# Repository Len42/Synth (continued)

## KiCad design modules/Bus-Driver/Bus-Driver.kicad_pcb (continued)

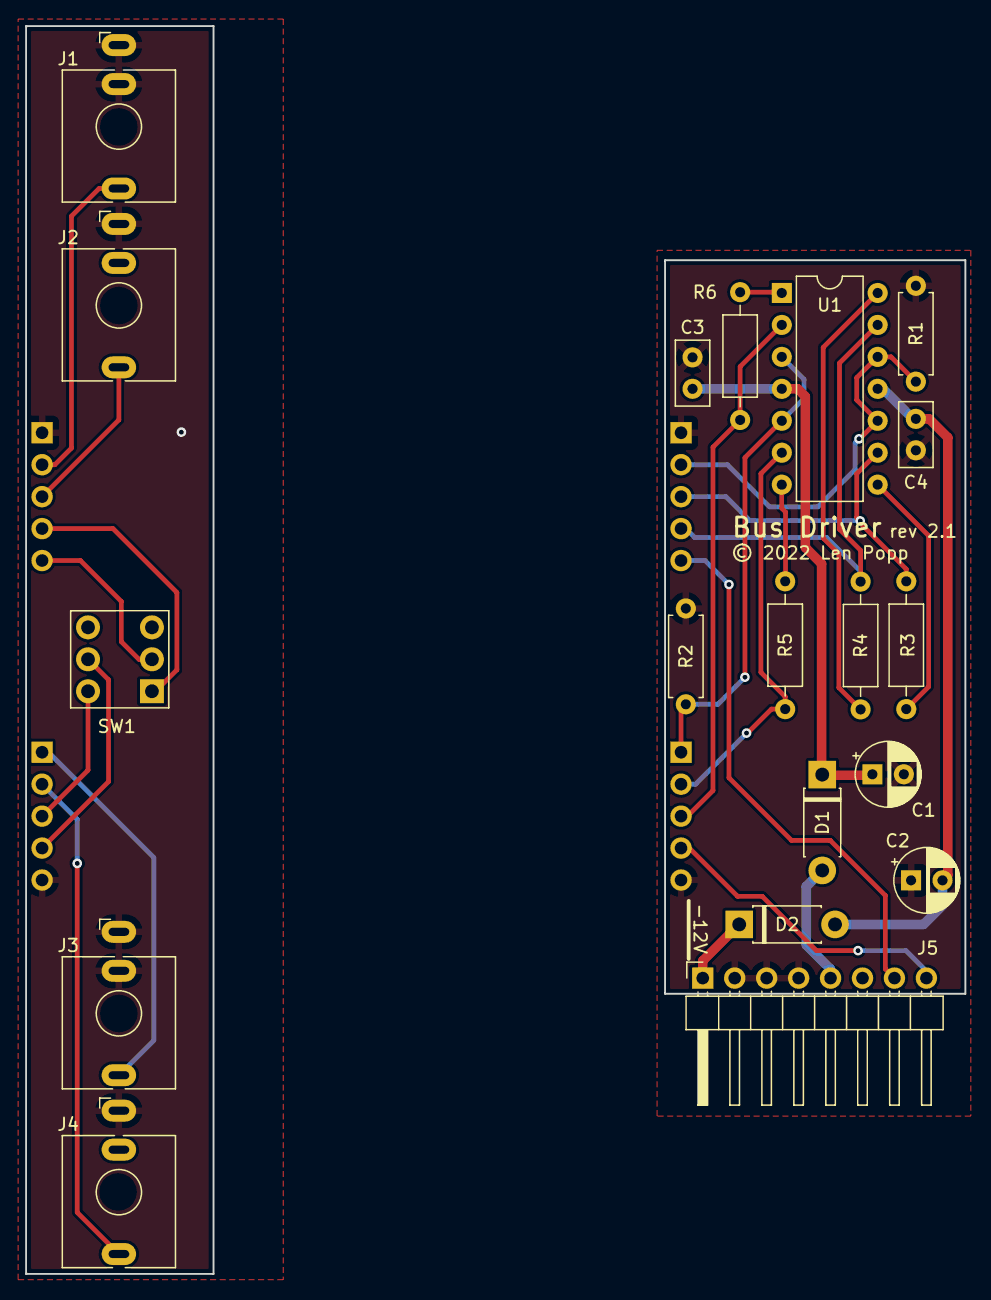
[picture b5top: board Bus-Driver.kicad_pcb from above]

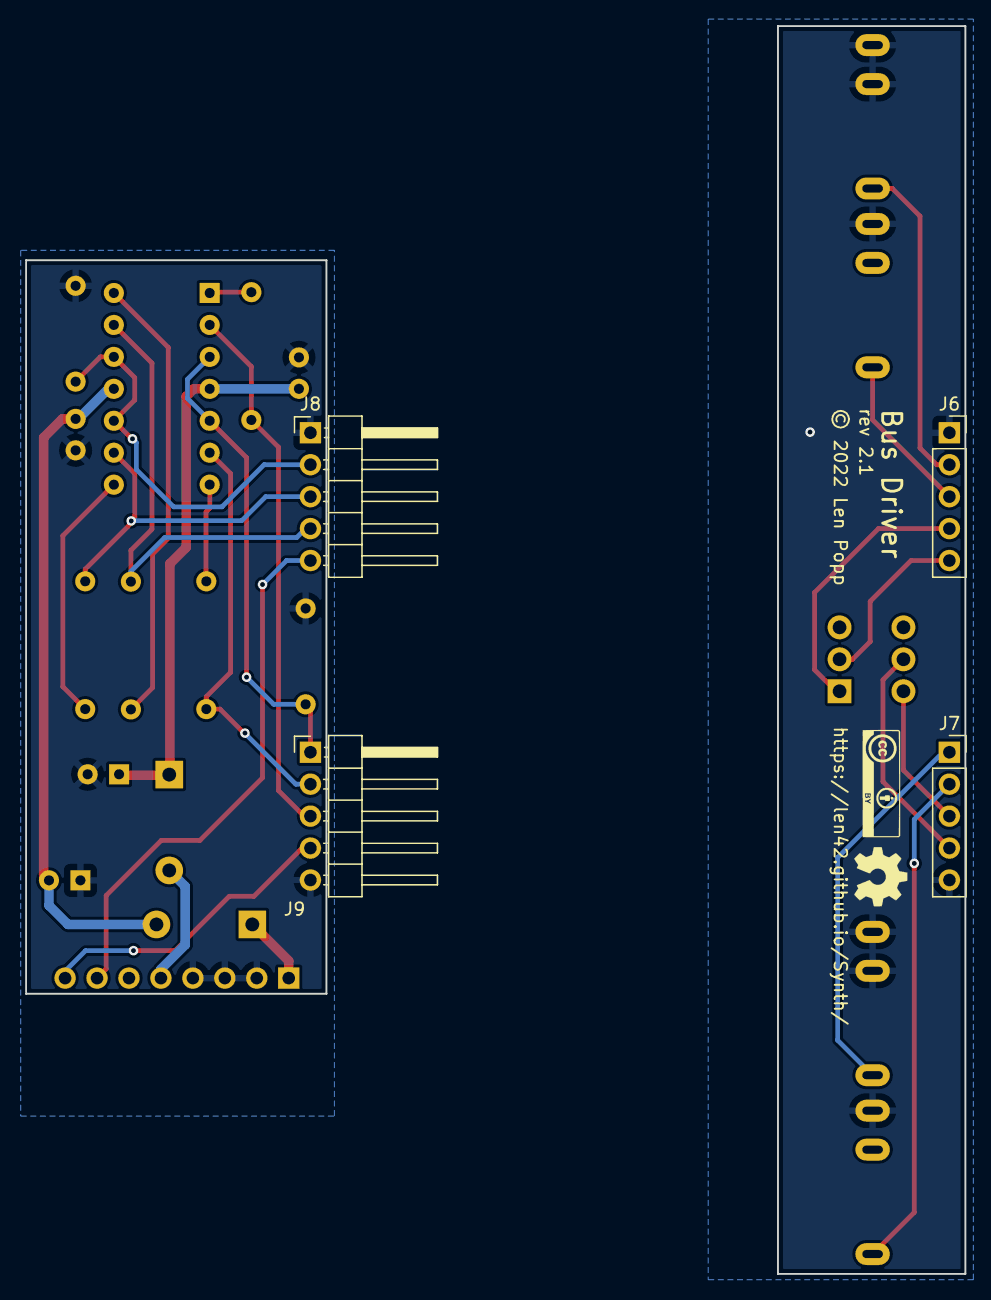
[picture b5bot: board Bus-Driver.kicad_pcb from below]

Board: 2 copper layers, 74.7 x 99.2 mm, 25 parts (6 on the bottom side), 17 nets.

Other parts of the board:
G2: Logo_CC_BY
G4: Logo_OSHW

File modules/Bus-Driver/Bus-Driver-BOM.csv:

Ref,Qty,Value,Value2,Note,Description,Datasheet,Manufacturer,ManuPartNum,Distributor1,DistributorPartNum1,DistributorPartLink1,Distributor2,DistributorPartNum2,DistributorPartLink2,Distributor3,DistributorPartNum3,DistributorPartLink3
"A1","1","Cable_Eurorack_16","","Length as required","Eurorack 16-16 pin power & bus cable","","","","Thonk","","https://www.thonk.co.uk/shop/eurorack-power-cables/","SynthCube","","https://synthcube.com/cart/eurorack-ribbon-power-cables","Modular Addict","","https://modularaddict.com/parts/eurorack-power-cables-1"
"C1","1","10U","35 VDC","12 V decoupling","Capacitor - Electrolytic - 12 V decoupling","https://www.mouser.ca/datasheet/2/315/ABA0000C1059-947582.pdf","Panasonic","ECE-A1VKS100I","Mouser","667-ECE-A1VKS100I","https://www.mouser.ca/ProductDetail/667-ECE-A1VKS100I","Thonk","Group_Eurorack_DIY_Essential","https://www.thonk.co.uk/shop/eurorack-diy-essentials/","","",""
"C2","1","10U","35 VDC","12 V decoupling","Capacitor - Electrolytic - 12 V decoupling","https://www.mouser.ca/datasheet/2/315/ABA0000C1059-947582.pdf","Panasonic","ECE-A1VKS100I","Mouser","667-ECE-A1VKS100I","https://www.mouser.ca/ProductDetail/667-ECE-A1VKS100I","Thonk","Group_Eurorack_DIY_Essential","https://www.thonk.co.uk/shop/eurorack-diy-essentials/","","",""
"C3 C4","2","100N","","IC decoupling","Capacitor - Ceramic - IC decoupling","https://product.tdk.com/system/files/dam/doc/product/capacit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","TDK","FG18X7R1H104KNT06","Mouser","810-FG18X7R1H104KNT6","https://www.mouser.ca/ProductDetail/810-FG18X7R1H104KNT6","","","","","",""
"D1 D2","2","MBR150","","","Schottky rectifier diode","https://www.onsemi.com/pdf/datasheet/mbr150-d.pdf","On Semi","MBR150RLG","Mouser","863-MBR150RLG","https://www.mouser.ca/ProductDetail/ON-Semiconductor/MBR150R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","","","","","",""
"J1 J2 J3 J4","4","WQP-PJ398","","","Audio Jack, 2 Poles (Mono / TS), Switched T Pole (Normalling), QingPu / Thonkiconn","http://www.qingpu-electronics.com/en/products/WQP-PJ398SM-362.html","QingPu / Thonk","PJ398SM / WQP518MA","Thonk","PJ398SM","https://www.thonk.co.uk/shop/thonkiconn/","SynthCube","WQP518MA","https://synthcube.com/cart/3-5mm-euro-jacks","Adafruit","4031","https://www.adafruit.com/product/4031"
"J5","1","Conn_01x08","","","Eurorack 8-pin board power/CV/gate bus connector","https://www.amphenol-icc.com/media/wysiwyg/files/documentati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","","","Adafruit","1540","https://www.adafruit.com/product/1540","Mouser","649-1012937993601BLF","https://www.mouser.ca/ProductDetail/Amphenol-FCI/10129379-93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","","",""
"J6 J7","2","Conn_Front","","","Generic connector, single row, 01x05, script generated (kicad-library-utils/schlib/autogen/connector/)","https://cdn-shop.adafruit.com/datasheets/00548.pdf","","","Adafruit","598","https://www.adafruit.com/product/598","Mouser","710-61303211821","https://www.mouser.ca/ProductDetail/Wurth-Elektronik/6130321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","","",""
"J8 J9","2","Conn_Back","","","Generic connector, single row, 01x05, script generated (kicad-library-utils/schlib/autogen/connector/)","https://www.amphenol-icc.com/media/wysiwyg/files/documentati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","","","Adafruit","1540","https://www.adafruit.com/product/1540","Mouser","649-1012937993601BLF","https://www.mouser.ca/ProductDetail/Amphenol-FCI/10129379-93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","","",""
"R1 R2","2","1M","1%, 1/6 W","","Resistor","https://www.mouser.ca/datasheet/2/447/Yageo_LR_MFR_1-1714151.pdf","YAGEO","MFR-12*","Mouser","603-MFR-12*","https://www.mouser.ca/c/?m=YAGEO&power+rating=166+mW+(1%2f6+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","","","","","",""
"R3","1","270R","1%, 1/4 W","Output limiting","Resistor","https://www.mouser.ca/datasheet/2/447/Yageo_LR_MFR_1-1714151.pdf","YAGEO","MFR-25FRF52-270R","Mouser","603-MFR-25FRF52-270R","https://www.mouser.ca/ProductDetail/603-MFR-25FRF52-270R","","","","","",""
"R4","1","270R","1%, 1/4 W","Output limiting","Resistor","https://www.mouser.ca/datasheet/2/447/Yageo_LR_MFR_1-1714151.pdf","YAGEO","MFR-25FRF52-270R","Mouser","603-MFR-25FRF52-270R","https://www.mouser.ca/ProductDetail/603-MFR-25FRF52-270R","","","","","",""
"R5","1","270R","1%, 1/4 W","Output limiting","Resistor","https://www.mouser.ca/datasheet/2/447/Yageo_LR_MFR_1-1714151.pdf","YAGEO","MFR-25FRF52-270R","Mouser","603-MFR-25FRF52-270R","https://www.mouser.ca/ProductDetail/603-MFR-25FRF52-270R","","","","","",""
"R6","1","270R","1%, 1/4 W","Output limiting","Resistor","https://www.mouser.ca/datasheet/2/447/Yageo_LR_MFR_1-1714151.pdf","YAGEO","MFR-25FRF52-270R","Mouser","603-MFR-25FRF52-270R","https://www.mouser.ca/ProductDetail/603-MFR-25FRF52-270R","","","","","",""
"SW1","1","SW_DPDT","","","Momentary Switch, dual pole double throw","https://www.carlingtech.com/sites/default/files/documents/Ca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","Carling","2S1-MDP1-T1-B1-M2QE","Mouser","10TC415","https://www.mouser.ca/ProductDetail/Mountain-Switch/10TC415?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","Antique Electronic Supply","P-H545-SUB","https://www.tubesandmore.com/products/switch-carling-submini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","Thonk","Group_SWITCH_DW","https://www.thonk.co.uk/shop/sub-mini-toggle-switches/"
"U1","1","TL074","","","Quad Low-Noise JFET-Input Operational Amplifiers, DIP-14/SOIC-14","http://www.ti.com/lit/ds/symlink/tl071.pdf","Texas Instruments","TL074BCN","Mouser","595-TL074BCN","https://www.mouser.ca/ProductDetail/?qs=vxEfx8VrU7BHurOY5iQd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","","","","","",""
